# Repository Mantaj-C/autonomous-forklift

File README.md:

## Autonomous Forklift Robot

This project was developed as part of the Electrical Systems Design course at BCIT. It features a fully autonomous forklift robot capable of identifying packages using ArUco markers and transporting them from an unsorted truck to the appropriate sorted location.

### Features:
- **C++ software** running on a **Raspberry Pi 4**
- **OpenCV + ArUco marker detection** for package identification
- **TCP/IP communication** between control modules
- **3D printed chassis and fork**, designed in **SolidWorks**
- **Custom PCB** for motor and sensor interfacing, built with **KiCad**
- **2 stepper motors** for drivetrain movement
- **4 servo motors** for lifting and package handling
- Onboard supervisor: **Tigger** 🐯

All STL files and C++ source code are included in this repository.

---

### 🔗 Project Demo
[Video Link](https://www.linkedin.com/posts/mantaj-chauhan-951b401b5_robotics-opencv-raspberrypi-activity-7332848276444012544-EtOq?utm_source=share&utm_medium=member_desktop&rcm=ACoAADIuHU0Bw7hjjBi1r9QsJ84nt98T_yjn1Ws)

---

### 📂 Contents
- `/src` – All C++ source code
- `/pcb` – KiCad PCB design files
- `/cad` – STL and SolidWorks files

---

### 🤝 Contributors
- [Mantaj Chauhan](https://www.linkedin.com/in/mantaj-chauhan-951b401b5/)
- [Fuquaan Hussein](https://www.linkedin.com/in/furqaan-hussein-994ba8367/)

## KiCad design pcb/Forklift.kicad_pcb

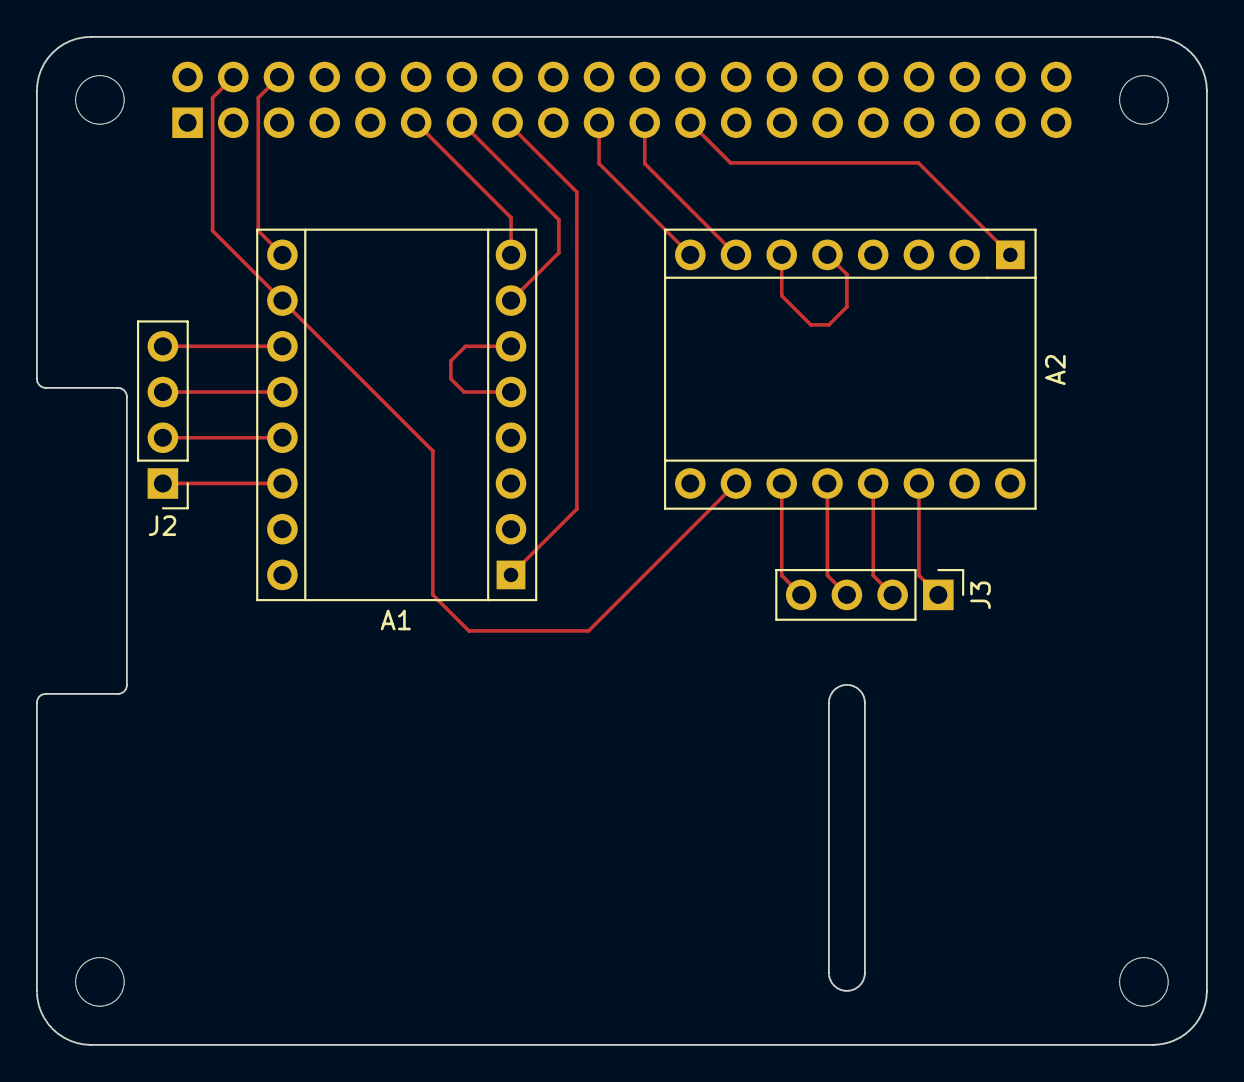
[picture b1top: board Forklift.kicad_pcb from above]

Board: 2 copper layers, 65.0 x 56.0 mm, 9 parts (1 on the bottom side), 21 nets.

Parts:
A1, A2: A4988_Motor_Driver; A4988_Motor_Driver-16_15.2x20.3mm
J1: GPIO; PinSocket_2x20_P2.54mm_Vertical
J2, J3: Conn_01x04; PinHeader_1x04_P2.54mm_Vertical
MH1, MH2, MH3, MH4: MountingHole_2.7mm_M2.5

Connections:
1A_01: A1.12 (1A), J2.3
1A_02: A2.12 (1A), J3.3
1B_01: A1.11 (1B), J2.4
1B_02: A2.11 (1B), J3.4
2A_01: A1.13 (2A), J2.2
2A_02: A2.13 (2A), J3.2
2B_01: A1.14 (2B), J2.1
2B_02: A2.14 (2B), J3.1
+3V3: J1.1, J1.17
DIR_01: A1.8 (DIR), J1.11
DIR_02: A2.8 (DIR), J1.19
EN_01: A1.1 (~ENABLE), J1.15
EN_02: A2.1 (~ENABLE), J1.23
GND_01: A1.9 (GND), A2.9 (GND), J1.6, J1.9, J1.14, J1.20, J1.25, J1.30, J1.34, J1.39
MS_01: A1.2 (MS1), A1.3 (MS2), A1.4 (MS3)
MS_02: A2.2 (MS1), A2.3 (MS2), A2.4 (MS3)
unnamed: A1.5 (~RESET), A1.6 (~SLEEP)
unnamed: A2.5 (~RESET), A2.6 (~SLEEP)
STEP_01: A1.7 (STEP), J1.13
STEP_02: A2.7 (STEP), J1.21
VDD_01: A1.10 (VDD), A2.10 (VDD), J1.2, J1.4

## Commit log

2025-05-25 Create temp
2025-05-25 Rename Fork_V4.SLDPRT to Fork_Structure.SLDPRT
2025-05-25 Rename Power_bank_holder.SLDPRT to Power_Bank_Holder.SLDPRT
2025-05-25 Rename ServoFork_Mirror_V2.SLDPRT to ServoFork.SLDPRT
2025-05-25 Rename aruco_holder.SLDPRT to Aruco_Plate.SLDPRT
2025-05-25 Rename motor_mount_fixed_fixed.SLDPRT to Stepper_Motor_Mount.SLDPRT
2025-05-25 Rename pi_walls.SLDPRT to Pi_Enclosure.SLDPRT
2025-05-25 Rename roller_wheel_attachment.SLDPRT to Roller_Wheel_Attachment.SLDPRT
2025-05-25 Rename Fork_V4.STL to Fork_Structure.STL
2025-05-25 Rename Power_bank_holder.STL to Power_Bank_Holder.STL
2025-05-25 Rename ServoFork_Mirror_V2.STL to ServoFork.STL
2025-05-25 Rename aruco_holder.STL to Aruco_Plate.STL
2025-05-25 Rename motor_mount_fixed_fixed.STL to Stepper_Motor_Mount.STL
2025-05-25 Rename pi_walls.STL to Pi_Enclosure.STL
2025-05-25 Rename roller_wheel_attachment.STL to Roller_Wheel_Attachment.STL
